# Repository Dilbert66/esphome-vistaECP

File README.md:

# Honeywell/Ademco Vista ECP ESPHome custom component and library

## Table of contents

- [Honeywell/Ademco Vista ECP ESPHome custom component and library](#honeywell-ademco-vista-ecp-esphome-custom-component-and-library)
  * [Table of contents](#table-of-contents)
  * [About the project](#about-the-project)
  * [Features](#features)
- [How to install](#how-to-install)
  * [⚠️ Warning!!! ⚠️](#⚠️-warning-⚠️)
  * [Prerequisites](#prerequisites)
    + [Identify Vista panel model](#identify-vista-panel-model)
  * [Project Structure and Wiring](#project-structure-and-wiring)
  * [Install ESPHome on the ESP device](#install-esphome-on-the-esp-device)
  * [Flash project into ESP device](#flash-project-into-esp-device)
    + [Language Adaptation](#language-adaptation)
      + [Option 1 (NEW)](#option-1--new-)
      + [Option 2 (OLD)](#option-2--old-)
  * [Connecting everything](#connecting-everything)
- [Miscellaneous](#miscellaneous)
  * [Example in Home Assistant](#example-in-home-assistant)
    + [Sample sensor configuration for card using mqtt](#sample-sensor-configuration-for-card-using-mqtt)
  * [HA Services](#ha-services)
  * [OTA updates](#ota-updates)
  * [MQTT integration](#mqtt-integration)
  * [Setting up the alarm panel keyboard card on HA](#setting-up-the-alarm-panel-keyboard-card-on-ha)
- [FAQ](#faq)
  * [Supported Models](#supported-models)
- [Report issue](#report-issue)
- [References](#references)
- [Author & Contributors](#author---contributors)

## About the project

This project allows you to monitor and control your old vista alarm panel over the internet through a cheap ESP device and an home automation platform such as Home Assistant or any other automation platform supporting the MQTT protocol.

If you like this project and wish to supplement my coffee intake, please click the button below to donate! Thank you!

Got a DSC PowerSeries panel? Have a look at the <a href="https://github.com/Dilbert66/esphome-dsckeybus">following project</a>.<br>

This is an implementation of an ESPHOME custom component and ESP Library to interface directly to Safewatch/Honeywell/Ademco Vista alarm systems using the ECP interface and very inexpensive ESP32 modules .  The ECP library code is based on the arduino source code from Mark Kimsal's repository located at  https://github.com/TANC-security/keypad-firmware.  It has been  completely rewritten as a class and adapted to work on the ESP platform using interrupt driven communications and pulse timing. A custom modified version of Peter Lerup's ESPsoftwareserial library (https://github.com/plerup/espsoftwareserial) was also used for the serial communications to work more efficiently within the tight timing of the ESP interrupt window. 

The panel sends various cmd packets such as the F7 (LCD display and status updates), FA (zone extenders, relay modules), FB (RF devices) and F2 (AUI touch screen diplays), F9 (Long range radio) and F6 (send keystrokes and cms).  These data cmds are used to capture all statuses from the panel as well as send keystrokes and cmds to the panel.

As far as writing on the bus and the request to send pulsing sequence, most documentation only discusses keypad traffic and this only uses the the 3rd pulse.  In actuality the pulses are used as noted below depending on the device type requesting to send:
```
Panel pulse 1. Addresses 1-7, expander board (07), etc
Panel pulse 2. Addresses 8-15 - zone expanders, relay modules
Panel pulse 3. Addresses 16-23 - keypads
```
For example, a zone expander that has the address 07, will send it's address on the first pulse only and will send nothing for the 2nd and 3rd pulse.  A keypad with address 16, will send a 1 bit pulse for pulse1 and pulse2 and then it's encoded address on pulse 3. This info was determined from analysis using a zone expander board and Pulseview to monitor the bus. 

If you are not familiar with ESPHome , I suggest you read up on this application at https://esphome.io and home assistant at https://www.home-assistant.io/.   The library class itself can be used outside of the esphome and home assistant systems.  Just use the code as is without the vistalalarm.yaml and vistaalarm.h files and call it's functions within your own application.  

This library is designed around the "external components" feature of ESPHome (https://esphome.io/components/external_components.html).  The previous version of this library was using the older "custom components" feature which is being deprecated.  Using external components is a much better alternative and allows for much easier install and customization.

To install, first copy the VistaAlarm.yaml file from here to your esphome directory. You can then edit it either directly or using the ESPHome dashboard to match your alarm panel setup.  The yaml is self explanatory.  Secondly, for the main library support code you have two choices:

 1: You can leave the yaml external_components source line uncommented and it will automatically fetch the required code from my esphome-components repository.  
 
 or alternatively:
 
 2: If you prefer a more manual approach, you can comment out the github source line and uncomment the source "my_components" line.  You will then need to create a matching my_components directory in your esphome home path.  Name it anything you like as long as it matches the source line in the yaml.  You then copy all content from the "components" directory located in repository https://github.com/Dilbert66/esphome-components/tree/main/ to this new directory.  Please note that for any future updates, you will again need to manually copy the files from the components repository to your esphome folder.

For multi partition support, it is important that you first program new keypad addresses assigned to each partiton you want to support using programs `*190` - `*196` on the vista panel.  Once done, assign these addresses to keypadaddr1 (partition1) , keypadaddr2 (partition2), keypaddr3 (partition3).  For unused partitions, leave the associated keypadaddrx config line at 0. 

##### Notes: 

* If you use the zone expanders and/or LRR functions, you might need to clear CHECK messages for the LRR and expanded zones from the panel on boot or restart by entering your access code followed by 1 twice. eg 12341 12341 where 1234 is your access code.

**Read more in the next wiki paragraphs for a detailed step by step guide.**

## Features

* Full zone expander emulation (4219/4229) which will give you  an additional 8 zones to the system per emulated expander plus associated relay outputs. Currently the library will provide emulation for 2 boards for a total of 16 additionals zones. You can even use free pins on the chip as triggers for those zones as well. 

* Full independent partition support. The firmware allows control and view status of all 3 partitions.

* Relay module emulation. (4204). The system can support 4 module addresses for a total of 16 relay channels. 

* Long Range Radio (LRR) emulation (or monitoring) statuses for more detailed status messages

* Zone status - Open, Alarmed, Closed and Bypass with named zones

* Arm, disarm or send any sequence of commands to the panel for any partition

* Status indicators - fire, alarm, trouble, armed stay, armed away, instant armed, armed night,  ready, AC status, bypass status, chime status,battery status, check status, zone and relay channel status field of individual partitions.

* Optional ability to monitor other devices on the bus such as keypads, other expanders, relay boards, RF devices, etc. This requires the #define MONITORTX to be uncommented in vista.h as well as the addition of two resistors (R4 and R5) to the circuit as shown in the schematic.   This adds another serial interrupt routine that captures and decodes all data on the green tx line.  If enabled this data will be used to update zone statuses for external modules.

The following services are published to home assistant for use in various scripts. 
```
alarm_disarm: Disarms the alarm with the user code provided, or the code specified in the configuration.
alarm_arm_home: Arms the alarm in home mode.
alarm_arm_away: Arms the alarm in away mode.
alarm_arm_night: Arms the alarm in night mode (no entry delay).
alarm_trigger_panic: Trigger a panic alarm.
alarm_trigger_fire: Trigger a fire alarm.
alarm_keypress: Sends a string of characters to the default partition. (Controlled by the keypad1 address)
alarm_keypress_partition: Sends a string of characters to any specified partition. (1, 2 or 3)
```

# How to install

## ⚠️ Warning!!! ⚠️

⚠️ **When opening the panel and dealing with the alarm panel itself throughout the reading of this wiki be careful as AC current is used to power the panel, make sure to switch it off before touching the terminals or any other part of the circuits.** ⚠️

##  Prerequisites

In order to install the project you need to:
- [Identify your Vista alarm panel model](#identify-vista-panel-model)
- Make sure to have a running instance of Home Assistant or any other home automation platform supporting MQTT protocol (or something else, but able to listen and publish on MQTT topics) // TO BE CHECKED
- [Get the needed components for the project and wire them](#project-structure-and-wiring)
- [Install ESPHome on the ESP device](#install-esphome-on-the-esp-device)
- Flash the project on the ESP device
- [Connect everything](#connecting-everything)

### Identify Vista panel model
Open the panel and check the interior side of the panel's door, there should be the wiring diagram indicating the Vista model right below (usually on bottom right or center). <br>

*Example: Vista-20P, Vista-20SE, Vista-20SEa, Vista-25IT, ...*<br>

If the wiring diagram is not present, check the circuit board. You should be able to see what model it is by looking either at the stamps/labels on the circuit board or by looking at the model on the CPU. The model here sometimes is in form of "SAVS**20P**5" or similar.<br> It is recommended to check also the circuit board even if you found the model on the wiring diagram, just to be sure that they match.

See image below, red arrows indicates where it could be.

Check [Supported Models](#supported-models) to get an overview of compatible models and continue to next section. 

If your device is not present in the list you could still try using one of the code versions available in the repository, **but the functioning is not guaranteed**.

Got a DSC PowerSeries panel? Have a look at the <a href="https://github.com/Dilbert66/esphome-dsckeybus">following project</a>.

##  Project Structure and Wiring

After you identified the vista panel's model then you can start preparing for the hardware part and the first HW part you need to get is an ESP device. In this case, it's highly
recommended that an ESP32 be used due to it's dual processor and increased available ram.<br>

Let's analyze the project structure.<br>

Currently the project is structured as follows:
- `master` branch: stable code - **recommended**
- `dev` branch: more updated code with new features, but WIP - **stability and functioning are not guaranteed**

For both branches you have the possibility to install them using Home Assistant or MQTT.<br>

If you have an Home Assistant instance running and you want to be able to fully control and monitor the panel through HA you will have to use the ESPHome yaml files for Home Assistant inside `src` folder. <br>

If instead you don't want to use Home Assistant, you can still use the component source code above, but you will have to use the sketch files inside the `MQTT-Example` folder and setup your home control software to process the MQTT topics.<br> // TO BE CHECKED

Select the branch and configuration/source code files you need.<br>

If you're unsure on what ESP model you need to get, then you can document at <a href="https://esphome.io/">ESPHome website</a>. *In theory*, any ESP device should work with ESPHome. Just make sure you have the GPIO numbers pin mapping, sometimes the pins don't match the ones reported in the pcb's silkscreen.<br>
*Example for the Wemos D1 R2 -> <a href="https://cyaninfinite.com/getting-started-with-the-wemos-d1-esp8266-wifi-board/">link</a>*

Now that you identified the panel, selected a source code and got an ESP device, it's time to choose a wiring configuration to the panel.

I've provided various working versions to fit within builders available parts or requirements.  None of these circuits need a pcb and can easily be built using point to point soldering on a proto board.

1. Non-isolated simple version.  Small parts count but resistor values are important.  Signal levels are dependent on components used. Output pulse will not be optimal due to optocoupler use.

2. Alternative version using transistors for both signal input and output.  Benefits are that signal quality will be optimal for both input and output. Resistor values are not critical. 
  Please note though that you have to configure your esphome yaml config accordingly to account for the signal inversion of this design. The other designs use the default settings.
YAML config:
```
  invert_mon: "false"
  invert_rx: "false"
  invert_tx: "true"
  input_mode_rx: INPUT_PULLUP
  input_mode_mon: INPUT_PULLUP
```

3. Ground isolated version

Notes: This version is the least recommended as it will load the ECP bus to a certain extent. It also does not provide the best signal output. This is all dependant on the bus it is connected to and the quality of the optocouplers used. Your mileage may vary.<br><br>
* Optocouplers should have a minimum CTR of 50. Recommendations are the 4N35 or TLP521. You can vary the resistor values for the simple version but keep the ratio similar for the voltage dividers R2/R3 and R4/R5. R1 should not be set below 150 ohm or 100ohm when using an ESP32. Resistor values are chosen to minimize load on ECP bus while still providing full output signals on the optocouplers. <br>
* My goal was to keep the design as simple as possible without causing any bus load or interference with maximum signal fidelity.  Since the transmit circuit required high side switching I opted to use an optocoupler since I had a few on hand and it simplified the amount of components needed but proved to have it's own issues as far as CTR requirements.  <br>

Read the notes on the drawings for more details.

Get the other components: 
- breadboard or PCB (if you prefer soldering)
- jumper cables
- 4-inputs screw terminal for the cables from the panel to the ESP (opt)
- resistors (you can use multiple resistors in series or parallel if you can't find kits with the exact value of the diagrams, i.e. 4.7KOhm can be obtained by using two resistors in parallel -> 100kohm + 5.1kohm =~ 4.8KOhm)
- optocouplers / transistors
- power supply or USB for the ESP device (highly recommended) or a 12V to 5V/3.3V regulator (to take the power from the panel)
- juction box (optional, to protect the ESP device if installed outside the panel)

Thanks to <a href="https://community.home-assistant.io/u/howardchen3">`@howardchen3`</a> there is a PCB layout of the ground-isolated version available at <a href="https://oshwlab.com/boobeechen/vistaesphome_copy">oshwlab</a> that could be used to send to a manufacturer. Read more on the site.

Wire the breadboard/PCB part according the wiring diagram you selected, but for the moment keep the ESP unplugged from both panel and breadboard/pcb since we're going to connect the ESP to the PC and it's not handy to have all the wires around. 

You should be in a situation like this now:

Esp is ready to be connected to the PCB/breadboard and the latter is ready to be connected at the panel.<br>
⚠️ **DO NOT CONNECT THEM YET** ⚠️

**Very important step**: Double check that the connections are ok (add some black tape to keep the loose connections in place if you opted for a breadboard). It is difficult to debug for HW problems once phisically attached to the panel or near to it as often the panels are not in comfy locations.

##  Install ESPHome on the ESP device
// TO BE CHECKED

This paragraph covers only the installation of the software that interacts with Home Assistant and ESPHome.

Connect the ESP device to the PC. Make sure you have the right drivers (CP2102 (square chip) or CH341 -> <a href="https://esphome.io/guides/physical_device_connection.html">ESPHome - physical device connection</a>) installed on your PC or ESPHome will not be able to recognize it.

Now you have two options:
1. Install a basic version of ESPHome on the ESP device (thorugh command line esphome or web.esphome.io) and then adopt it on ESPHome of your HA instance (in order to install right after the needed software over the air) **OR**
2. Install the final project on the device by using the ESPHome addon on HA (might be required to connect the ESP on the PC that is running HA)

Before proceeding with any of the two options, make sure to identify the right board and framework (opt) for your ESP device. Check the ESPHome website for more info.<br>

## Connecting everything 

⚠️ **Before continuing read [Warning notice](#⚠️-warning-⚠️)** ⚠️

Let's connect the ESP device to the breadboard or PCB and finally let's connect the breadboard/PCB to the panel. Depending on the configuration you selected, you need to connect the breadboard/PCB to the same keypad terminals of your existing physical keyboard **OR**, if you prefer, on the keypad terminals of another partition of your panel (in case of multi-partition panel).

**Make sure to keep the ESP device further from any RF receiver as the components and the ESP itself could cause interference.**

Power up the ESP device and check on Home Assistant. In a minute or so it should be ready and accessible from HA > ESPHome.

Ping the device address if having problems and double check the `project_config.yaml` file.

**Optional steps**

Cover the ESP device with a junction box or similar just to make a cover. Remember to keep at least two holes for some air venting.

Final result:

Note: Even the circuitry can be placed outside if you want. The wires from circuitry to the ESP are just for demo purposes, not related at all to the wiring diagrams. The power wire depends on the setup you chose, but it's recommended to have an external power supply.

# Miscellaneous
## Example in Home Assistant
#Note: The config below assumes an ESPHOME device named: "vistaalarm". Change the lines below to suit your own device name.

The returned statuses for Home Assistant are: armed_away, armed_home, armed_night, pending, disarmed,triggered and unavailable.  

Sample Home Assistant Template Alarm Control Panel configuration with simple services (defaults to partition 1):

```yaml
alarm_control_panel:
  - platform: template
    panels:
      safe_alarm_panel:
        name: "Alarm Panel"
        value_template: "{{states('sensor.vistaalarm_system_status')}}"
        code_arm_required: false
        
        arm_away:
           action: esphome.vistaalarm_alarm_arm_away
                  
        arm_home:
           action: esphome.vistaalarm_alarm_arm_home
          
        arm_night:
           action: esphome.vistaalarm_alarm_arm_night
            data_template:
              code: '{{code}}' #if you didnt set it in the yaml, then send the code here
          
        disarm:
           action: esphome.vistaalarm_alarm_disarm
            data_template:
              code: '{{code}}'                    
```

##  HA Services
Note:  The services for the HA API  will show up as esphome.<yourdevicename>.<servicenamefromlistbelow>
- Basic alarm services. These services default to partition 1:

	- "alarm_disarm", Parameter: "code" (access code)
	- "alarm_arm_home" 
	- "alarm_arm_night", Parameter: "code" (access code)
	- "alarm_arm_away"
	- "alarm_trigger_panic"
	- "alarm_trigger_fire"

- Intermediate command service. Use this service if you need more versatility such as setting alarm states on any partition:

	- "set_alarm_state",  Parameters: "partition","state","code"  where partition is the partition number from 1 to 8, state is one of "D" (disarm), "A" (arm_away), "S" (arm_home), "N" (arm_night), "P" (panic) or "F" (fire) and "code" is your panel access code (can be empty for arming, panic and fire cmds )

- Generic command service. Use this service for more complex control:

	- "alarm_keypress",  Parameter: "keys" where keys can be any sequence of keys accepted by your panel. For example to arm in night mode you set keys to be "xxxx33" where xxxx is your access code. 
    
	- "alarm_keypress_partition",  Parameters: "keys","partition" where keys can be any sequence of keys accepted by your panel and partition is  1 - 3. For example to arm in night mode  on partition 1 you set keys to be "xxxx33" and partition to be "1"  where xxxx is your access code.     
    
  - "set_zone_fault",Parameters: "zone","fault" where zone is a zone from 9 - 48 and fault is 0 or 1 (0=ok, 1=open)
      The zone number will depend on what your expander address is set to.

## OTA updates

In order to make OTA updates, it is recommended that the connection switch in the frontend be switched to OFF since the  ECP library is using interrupts and could cause issues with the update process.

## MQTT Support
If you would like to use MQTT communications with Homeassistant or alternatively use ESPHOME with other platforms that can support MQTT, you can modify the configuration to use the MQTT protocol instead of the native HA API integration.  This simply involves the addtion of an mqtt: configuration section in the yaml and to remove the api: section.   Please see the ESPHOME MQTT documentation more details: https://esphome.io/components/mqtt.html .  For an example on how to configure the alarm-panel-card to use MQTT services, please see the lovelace.yaml file.  

Command topic is "&lt;yoursystemnameinesphome&gt;/alarm/set"
	
Command payload for sending key commands: {"keys":"&lt;sequenceofkeys&gt;","partition":&lt;partition#&gt;}
	
Command payload to set an expander fault status: {"zone":&lt;zone#&gt;,"fault":&lt;on:off or 0:1&gt;}
	
Command payload to set an alarm state: {"state":"&lt;alarmstate&gt;","partition":&lt;partition#&gt;,"code":"&lt;accesscode&gt;"} - see set_alarm_state api command above for more details

Sensor data will follow the HA MQTT discovery format. See here for details: https://www.home-assistant.io/docs/mqtt/discovery/

If you prefer to use Arduino instead of ESPHome, I've also provided an Arduino example sketch in the mqtt_example folder.  Follow the instructions at the top of the file.

### Sample sensor configuration for card using mqtt.
Note, in this example the ESPHOME device name is "vistaalarm". Please change the lines below to match your own device name and field id's.

```yaml
# Partition 1 topics

mqtt:
  sensor:
    - name: "displayline1"
      state_topic: "vistaalarm/sensor/line1__ln1_1/state

    - name: "displayline2"
      state_topic: "vistaalarm/sensor/line2_ln2_1/state"

    - name: "vistaaway"
      state_topic: "vistaalarm/binary_sensor/away_partition_1/state"

    - name: "vistastay"
      state_topic: "vistaalarm/binary_sensor/stay_partition_1/state"

    - name: "vistaready"
      state_topic: "vistaalarm/binary_sensor/ready_partition_1/state"

    - name: "vistatrouble"
      state_topic: "vistaalarm/binary_sensor/trouble_partition_1/state"

    - name: "vistabypass"
      state_topic: "vistaalarm/binary_sensor/bypass_partition_1/state"

    - name: "vistachime"
      state_topic: "vistaalarm/binary_sensor/chime_partition_1/state"
      
    - name: "vistabeeps"
      state_topic: "vistaalarm/sensor/beeps_partition_1/state"    

    - name: "vistaac"
      state_topic: "vistaalarm/binary_sensor/ac_status/state" 

    - name: "vistabattery"
      state_topic: "vistaalarm/binary_sensor/battery_status/state"
      
    - name: "Front Door"
      state_topic: "vistaalarm/binary_sensor/front_door_z1/state"       

```

##  Setting up the alarm panel keyboard card on HA

I've added a sample lovelace alarm-panel card copied from the repository at https://github.com/GalaxyGateway/HA-Cards. I've customized it to work with this ESP library's services.   I've also added two new text fields that will be used by the card to display the panel prompts the same way a real keypad does. To configure the card, just place the `alarm-keypad-card.js` and `*.mp3` files from the ha_keypad_card folder into the `/config/www` directory of your homeassistant installation and add a new resource in your lovelace configuration pointing to `/local/alarm-keypad-card.js`. <br>
Add a reference to alarm-keypad-card.js in Lovelace. There’s two way to do that:<br>
1. Using UI:  go to settings (cog icon bottom left in sidebar menu), click on 'dashboards', click on top right 3 dots option then on Resources,
  bottom right 'add resource' option, in window, paste the url as '/local/alarm-keypad-card.js?id=1', select javascript module.

3. Using YAML: Add following code to lovelace section

```yaml
resources:
- url: /local/alarm-keypad-card.js?id=1
  type: module
```
*** NOTE *** :  Every time you update this file, you will need to increase the id=xx number in the url by 1 in order to force the browser to reload it.

You can then configure the card as shown below. Just substitute your service name to your application and choose one of the two chunks.

The first example is for using the esphome component in a multi partition environment.  The second uses MQTT.  The MQTT example can also support multiple partitions. 
Simply add "partition":xx in the json payload to select the desired partion where xx is the partition number.  If you don't enter a partition value, the default partition of 1 will be used.

```yaml
# EX1 - Partition 1 example - HA
type: custom:alarm-keypad-card
title: Vista_ESPHOME-partition1
disp_line1: sensor.vistaalarmtest_line1
disp_line2: sensor.vistaalarmtest_line2
service_type: esphome
service: vistaalarm_alarm_keypress_partition
status_A: AWAY
status_B: STAY
status_C: READY
status_D: BYPASS
status_E: TROUBLE
status_F: CHIME
status_G: ""
status_H: ""
sensor_A: binary_sensor.vistaalarmtest_away
sensor_B: binary_sensor.vistaalarmtest_stay
sensor_C: binary_sensor.vistaalarmtest_ready
sensor_D: binary_sensor.vistaalarmtest_bypass
sensor_E: binary_sensor.vistaalarmtest_trouble
sensor_F: binary_sensor.vistaalarmtest_chime
button_A: STAY
button_B: AWAY
button_C: BP LIST
button_D: BYPASS
button_F: null
button_G: ""
button_E: ""
button_H: DISARM
status_C_off_icon: mdi:circle-off-outline
status_C_on_icon: mdi:check-circle
status_C_color: green
status_E_color: orange
status_E_on_icon: mdi:alert
status_E_off_icon: mdi:triangle-outline
status_B_color: red
status_B_on_icon: mdi:shield-lock
status_B_off_icon: mdi:shield-off-outline
status_A_color: red
status_A_on_icon: mdi:shield-lock
status_A_off_icon: mdi:shield-off-outline

#all style settings are optional. These are the default colors
style:
  "--lcdbgcolordark": var(--input-fill-color)
  "--lcdtextcolordark": var(--primary-text-color)
  "--buttonbgcolordark": var(--input-fill-color)
  "--buttontextcolordark": var(--primary-color)
  "--buttonhovercolordark": var(--outline-hover-color)
  "--buttonactivecolordark": var(--secondary-text-color)
  "--sensorlabelcolordark": var(--accent-color));
  "--buttonfocuscolordark": var(--outline-color)
  "--sensoroffcolordark": var(--disabled-text-color)
  "--bordercolordark": var(--disabled-color)

  "--sensoroffcolorlight": var(--disabled-text-color)
  "--lcdbgcolorlight": var(--input-fill-color)
  "--lcdtextcolorlight": var(--primary-text-color)
  "--sensorlabelcolorlight": var(--accent-color));
  "--buttonbgcolorlight": var(--input-fill-color)
  "--buttontextcolorlight": var(--primary-color)
  "--buttonhovercolorlight": var(--outline-hover-color)
  "--buttonactivecolorlight": var(--secondary-text-color)
  "--buttonfocuscolorlight": var(--outline-color)
  "--bordercolorlight": var(--disabled-color)

cmd_A:
  keys: "12343"
  partition: 1
cmd_B:
  keys: "12342"
  partition: 1
cmd_C:
  keys: 1234600
  partition: 1
cmd_D:
  keys: 12346#
  partition: 1
cmd_E:
  keys: A
  partition: 1
cmd_H:
  keys: 12341
  partition: 1
cmd_F:
  keys: <
  partition: 1
cmd_G:
  keys: ">"
  partition: 1
key_0:
  keys: "0"
  partition: 1
key_1:
  keys: "1"
  partition: 1
key_2:
  keys: "2"
  partition: 1
key_3:
  keys: "3"
  partition: 1
key_4:
  keys: "4"
  partition: 1
key_5:
  keys: "5"
  partition: 1
key_6:
  keys: "6"
  partition: 1
key_7:
  keys: "7"
  partition: 1
key_8:
  keys: "8"
  partition: 1
key_9:
  keys: "9"
  partition: 1
key_star:
  keys: "*"
  partition: 1
key_pound:
  keys: "#"
  partition: 1
text_1: "OFF"
text_2: AWAY
text_3: STAY
text_4: MAX
text_5: TEST
text_6: BYPASS
text_7: INSTANT
text_8: CODE
text_9: CHIME
text_star: READY
text_pound: ""
text_0: ""
scale: 1
button_disabled_A: false
button_disabled_B: false
button_disabled_C: false
button_disabled_D: false
button_disabled_E: true
button_disabled_F: true
button_disabled_G: true
button_disabled_H: true
beep: sensor.vistaalarmtest_beeps
view_pad: true
view_display: true
view_status: true
view_status_2: true
view_bottom: false
button_left: false
vibration_duration: 5

```

```yaml
# EX2 - Partition 1 example - MQTT

type: 'custom:alarm-keypad-card'
title: Vista_MQTT
unique_id: vista1
disp_line1: sensor.displayline1
disp_line2: sensor.displayline2
scale: 1
service_type: mqtt
service: publish
status_A: AWAY
status_B: STAY
status_C: READY
status_E: BYPASS
status_D: TROUBLE
status_F: ''
status_G: ''
status_H: ''
sensor_A: sensor.vistaaway
sensor_B: sensor.vistastay
sensor_C: sensor.vistaready
sensor_E: sensor.vistabypass
sensor_D: sensor.vistatrouble
button_A: STAY
button_B: AWAY
button_C: DISARM
button_D: BYPASS
cmd_A:
  topic: Vista/Set
  payload: '{"keys":"12343","partition":"1"}
cmd_B:
  topic: Vista/Set
  payload: '{"keys":"12342","partition":"1"}
cmd_C:
  topic: Vista/Set
  payload: '{"keys":"12341","partition":"1"}
cmd_D:
  topic: Vista/Set
  payload: '{"keys":"12346#","partition":"1"}
key_0:
  topic: Vista/Set
  payload: '{"keys":"0","partition":"1"}
key_1:
  topic: Vista/Set
  payload: '{"keys":"1","partition":"1"}
key_2:
  topic: Vista/Set
  payload: '{"keys":"2","partition":"1"}
key_3:
  topic: Vista/Set
  payload: '{"keys":"3","partition":"1"}
key_4:
  topic: Vista/Set
  payload: '{"keys":"4","partition":"1"}
key_5:
  topic: Vista/Set
  payload: '{"keys":"5","partition":"1"}
key_6:
  topic: Vista/Set
  payload: '{"keys":"6","partition":"1"}
key_7:
  topic: Vista/Set
  payload: '{"keys":"7","partition":"1"}
key_8:
  topic: Vista/Set
  payload: '{"keys":"8","partition":"1"}
key_9:
  topic: Vista/Set
  payload: '{"keys":""9,"partition":"1"}
key_star:
  topic: Vista/Set
  payload: '{"keys":"*","partition":"1"}
key_pound:
  topic: Vista/Set
  payload: '{"keys":"#","partition":"1"}
text_1: 'OFF'
text_2: AWAY
text_3: STAY
text_4: MAX
text_5: TEST
text_6: BYPASS
text_7: INSTANT
text_8: CODE
text_9: CHIME
text_star: READY
text_pound: ''
text_0: ''  
view_pad: true
view_display: true
view_status: true
view_status_2: true
view_bottom: false
button_left: false
beep: sensor.vistabeeps
vibration_duration: 5
```

# FAQ

1. How do I use the Trace Analyzer for deeper investigation?

Connect the pulseview channel D0 to the yellow line input on the D1 ESP input pin and the pulseview channel D1 to the green line monitor input D5 pin on ESP and then finally ground to the common ground on the ESP side. You don't need to monitor VCC or the ESP D2 output since that will also be seen on the green line monitor input at D5. Make sure you don't connect the channel inputs to any voltage higher than around 5 volts.

You should not be sharing ground between the panel and the esp if you used the optocoupler isolated schematic to build your circuit. if you did, it won't hurt anything, it's just not needed.

The setup file is really just the decoder setup so you that you can actually see the data being sent. It's attached below.
Just unzip it and load it into PulseView software by selecting "Restore session setup" from the menu. Ensure you connect your device first before running PulseView so that it picks it up on start up. (it will show up as a Saelea 8 channel). Once it starts your session, you will see 8 inputs. Once you restore the saved session setup, you will see 3 channels and 2 decoders. One for the panel (yellow line) and one for the keypad (green line). You'll need to run the capture twice to actually capture data. Seems like the first time after loading a session, it does not see the channels but the second run is fine.

<a href="https://github.com/Dilbert66/esphome-vistaECP/files/7150101/vistaecp2.zip">vistaecp2.zip</a>

Once you have about 1 minute or so of data you can then click the save button to save the session. It will create an *.sr file.
zip that and attach it to the issue.

### sample sensor configuration for card using mqtt

2. What is LRR?

LRR = Long Range Radio. IP or GSM interface and monitored by a central monitoring station.

3. What is an address?

A zone number. Zone number = Address. //TO BE CHECKED

4. How do I setup the expanders?

// TO BE CHECKED

5. What is the access code?

Your 4 digit secret number to arm/disarm the system. e.g. 1234

6. What is quickArm?

It will the hashtag instead of your access code for the arm command. E.g. it will send #3 instead of 12343 to enable "stay" mode.

7. What is RFMsg?

It is a string variable that will be populated with the messages from your RF devices, if any. Read more in the yaml configuration section (rfSerialLookup).<br>
In general, the RF message will contain the serial number and a status byte (with the sensor data).<br>
```
  bit 1 - ?
  bit 2 - Battery (0=Normal, 1=LowBat)
  bit 3 - Heartbeat (Sent every 60-90min) (1 if sending heartbeat)
  bit 4 - ?
  bit 5 - Loop 3 (0=Closed, 1=Open)
  bit 6 - Loop 2 (0=Closed, 1=Open)
  bit 7 - Loop 4 (0=Closed, 1=Open)
  bit 8 - Loop 1 (0=Closed, 1=Open)
```
// TO BE CHECKED

8. How do I open an issue?

See [How to](#report-issue) section.

```

## Supported Models

As of today:

|  **Model** |  **Source Code**  |
|:----------:|:-----------------:|
| Vista 20P  | vistaEcpInterface |
| Vista 20SE | vista20SE         |
| Vista 25IT | vista20SE         |
| Vista120 | vistaEcpInterface - // TO BE CHECKED |
| Vista128bpt/250bpt | vistaEcpInterface - // TO BE CHECKED |
| | |
| | |
| | |
| | |

# Report issue

First: search for your issue into the closed and open issues in the repo, if you don't find anything, open a new issue specifying:<br>
- Panel Model
- Used ESP model
- Used wiring diagram
- YAML config (the necessary parts)
- Issue
- Installed sensors (if relevant)
- What you've tried
- Logs

# References

## References 

You can checkout the links below for further reading and other implementation examples. Some portions of the code in the repositories below was used in creating the library.
* https://github.com/TANC-security/keypad-firmware
* https://github.com/cweemin/espAdemcoECP
* https://github.com/TomVickers/Arduino2keypad/

This project is licensed under the `Lesser General Public License` version `2.1`, or (at your option) any later version as per it's use of other libraries and code. Please see `COPYING.LESSER` for more information.

# Author & Contributors

- @Dilbert66 (Author)
- @appleguru (Contributor)
- @nitej (Contributor)
- @rcmurphy (Contributor)
- @jdev-homeauto (Contributor)
- @lorenzodeveloper (Contributor)

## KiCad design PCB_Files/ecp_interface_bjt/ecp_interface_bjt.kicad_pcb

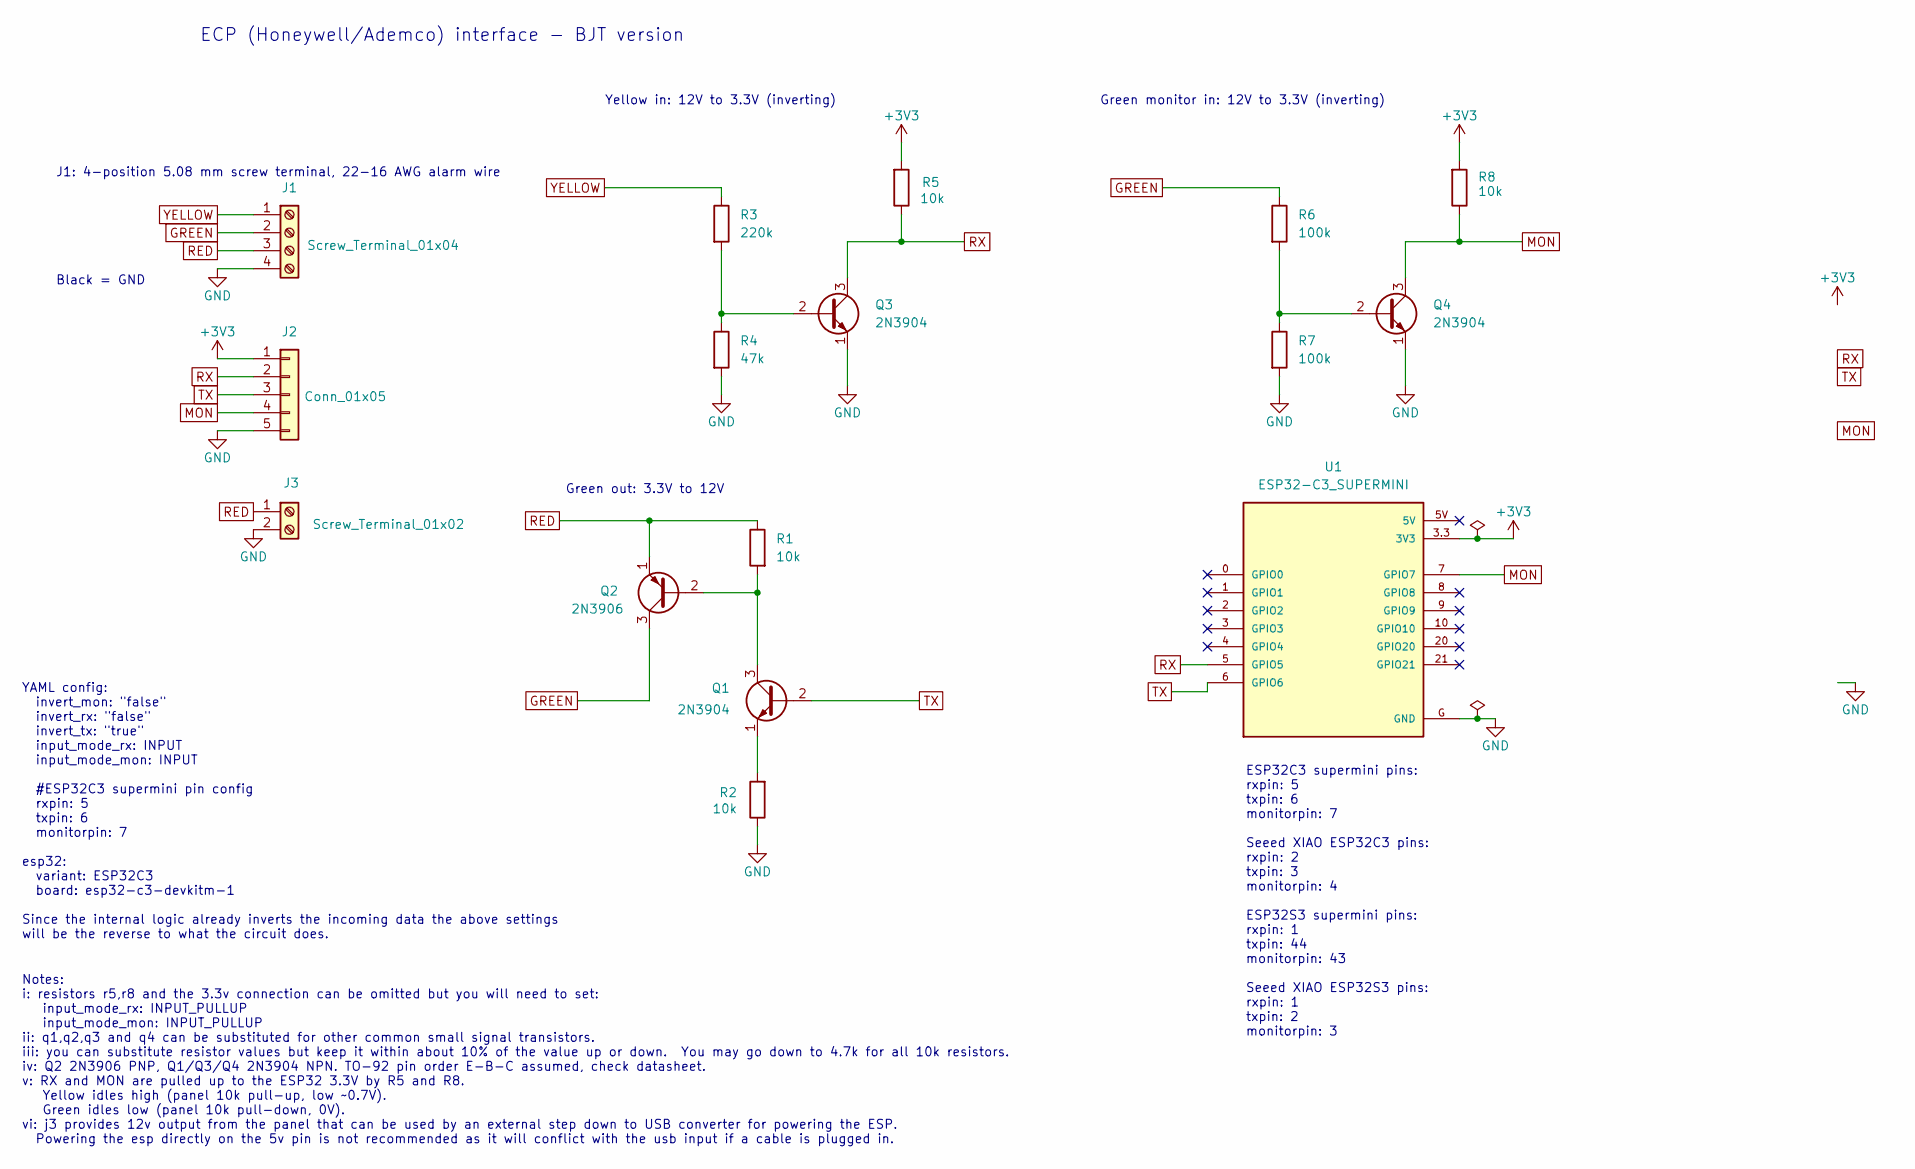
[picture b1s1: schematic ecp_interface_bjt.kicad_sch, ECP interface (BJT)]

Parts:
J1: Screw_Terminal_01x04; TerminalBlock_MetzConnect_Type101_RT01604HBWC_1x04_P5.08mm_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
J2: Conn_01x05; PinHeader_1x05_P2.54mm_Vertical
J3: Screw_Terminal_01x02; TerminalBlock_MetzConnect_Type059_RT06302HBWC_1x02_P3.50mm_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
Q1, Q3, Q4: 2N3904; TO-92_HandSolder
Q2: 2N3906; TO-92_HandSolder
R1, R2, R5, R8: 10k; R_Axial_DIN0207_L6.3mm_D2.5mm_P10.16mm_Horizontal
R3: 220k; R_Axial_DIN0207_L6.3mm_D2.5mm_P10.16mm_Horizontal
R4: 47k; R_Axial_DIN0207_L6.3mm_D2.5mm_P10.16mm_Horizontal
R6, R7: 100k; R_Axial_DIN0207_L6.3mm_D2.5mm_P10.16mm_Horizontal
U1: ESP32-C3_SUPERMINI; MODULE_ESP32-C3_SUPERMINI_PIN1

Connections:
+3V3: J2.1, R5.2, R8.2, U1.3.3 (3V3)
GND: J1.4, J2.5, J3.2, Q3.1 (E), Q4.1 (E), R2.1, R4.2, R7.2, U1.G (GND)
GREEN: J1.2, Q2.3 (C), R6.1
MON: J2.4, Q4.3 (C), R8.1, U1.7 (GPIO7)
unnamed: Q1.3 (C), Q2.2 (B), R1.2
unnamed: Q1.1 (E), R2.2
unnamed: Q3.2 (B), R3.2, R4.1
unnamed: Q4.2 (B), R6.2, R7.1
RED: J1.3, J3.1, Q2.1 (E), R1.1
RX: J2.2, Q3.3 (C), R5.1, U1.5 (GPIO5)
TX: J2.3, Q1.2 (B), U1.6 (GPIO6)
YELLOW: J1.1, R3.1

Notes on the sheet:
J1: 4-position 5.08 mm screw terminal, 22-16 AWG alarm wire
Yellow in: 12V to 3.3V (inverting)
Notes: i: resistors r5,r8 and the 3.3v connection can be omitted but you will need to set: input_mode_rx: INPUT_PULLUP input_mode_mon: INPUT_PULLUP ii: q1,q2,q3 and q4 can be substituted for other common small signal transistors. iii: you can substitute resistor values but keep it within about 10% 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
ECP (Honeywell/Ademco) interface - BJT version
Black = GND
Green monitor in: 12V to 3.3V (inverting)
ESP32C3 supermini pins: rxpin: 5 txpin: 6 monitorpin: 7 Seeed XIAO ESP32C3 pins: rxpin: 2 txpin: 3 monitorpin: 4 ESP32S3 supermini pins: rxpin: 1 txpin: 44 monitorpin: 43 Seeed XIAO ESP32S3 pins: rxpin: 1 txpin: 2 monitorpin: 3
Green out: 3.3V to 12V
YAML config: invert_mon: "false" invert_rx: "false" invert_tx: "true" input_mode_rx: INPUT input_mode_mon: INPUT #ESP32C3 supermini pin config rxpin: 5 txpin: 6 monitorpin: 7 esp32: variant: ESP32C3 board: esp32-c3-devkitm-1 Since the internal logic already inverts the incoming data the above setti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

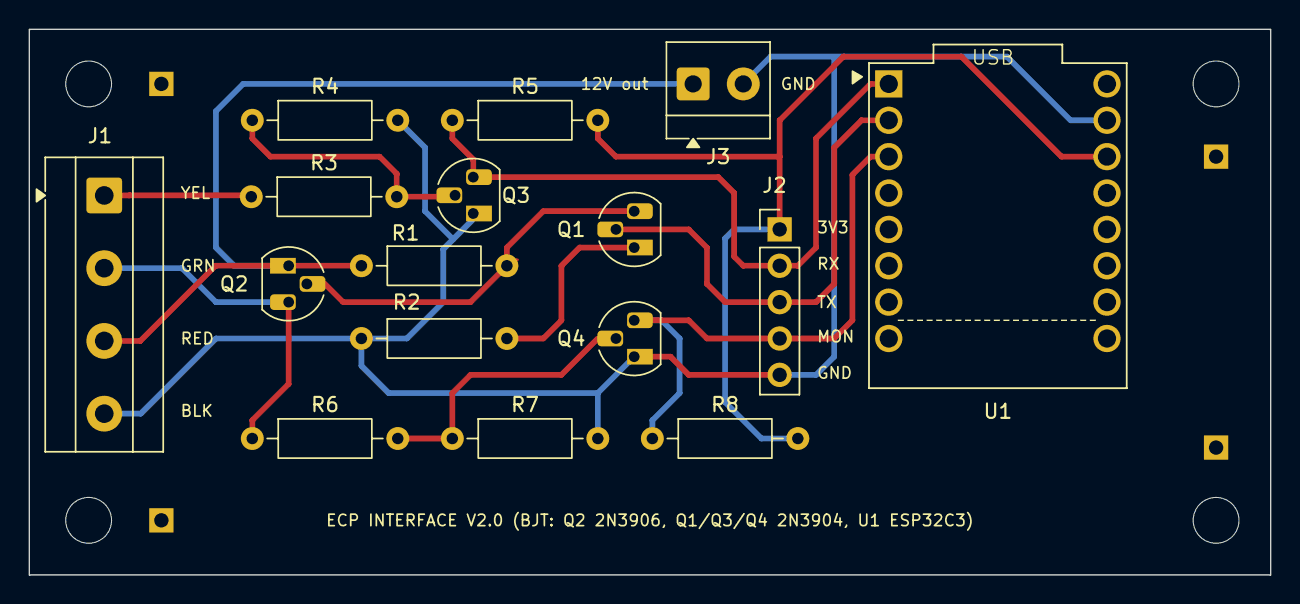
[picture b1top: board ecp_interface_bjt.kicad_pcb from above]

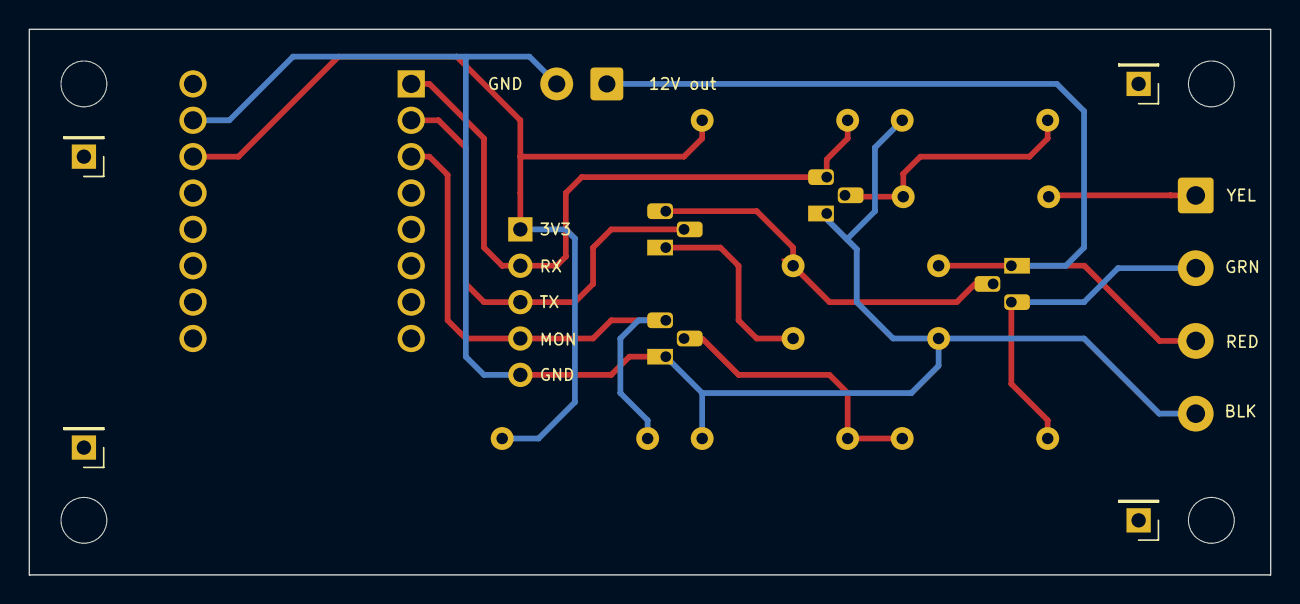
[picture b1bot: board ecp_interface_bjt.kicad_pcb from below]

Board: 2 copper layers, 86.7 x 38.1 mm, 24 parts (4 on the bottom side), 12 nets.

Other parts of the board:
H1, H2, H3, H4: MountingHole_3.2mm_M3
js: support pin; PinHeader_1x01_P2.54mm_Vertical
js#2, js#3, js#4: support pin; PinHeader_1x01_P2.54mm_Vertical

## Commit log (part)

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2022-04-11 - fixed issue with system flag statuses
2022-04-11 - fixed incorrect battery flag logic
2022-04-13 - simplified binary zone sensor example by adding new dedicated callback - updated example yaml
2022-04-16 - modified partition check to allow zone messages to pass through
2022-04-16 -added missed vistalarm.h changes
2022-04-18 - removed last change to display all zones. Limit to partition assigned to virtual keypad only
2022-04-18 - added ability to enter lookup strings as character arrays instead of strings to simplify adding non-english type messages
2022-04-18 - modified lookup strings to be editable as ascii characters
2022-04-18 - small change to lookup
2022-04-18 - small change
2022-04-18 - only display ascii line for zone messages
2022-04-18 - removed unecessary armed prompt check
2022-04-19 - removed high range filter from prompt characters to allow international characters
2022-04-19 - removed filter in SE lib
2022-04-19 - modified translate code to filter out non ascii as they cause issues. Add ability to translate specific characters
2022-04-19 - translation change to fully remove problematic asci characters
2022-04-20 - reverted to string lookup entries due to the non-ascii characters changing the string
2022-05-02 - corrected missing check status - added missing armed sensor statement - corrected away status update
2022-05-02 - changed alarm setting services to now be required to send the partition to support multi partions. - added field refresh to rf and beeps to force them to a known value at start and to clear the pre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
2022-05-02 - small tweak on trouble status logic - added problem device type to trouble
2022-05-09 Added HA card simulating a 6139 keypad
2022-05-11 - added real time clock to data logging
2022-05-12 - added example commented api encryption config
2022-06-15 - added ability to trigger panic keys (zone 95,96,99) by sending keys F,M or P (fire,medical,police)
2022-06-15 - remove uneeded code
2022-10-03 - typo in alarmstatus assignment
2022-10-03 - removed uneeded service. - removed duplicate entry in yaml file
2022-10-03 - changed f7 to fe command processing
2022-10-03 - default se to partition 1 - added missing keypadaddress section to single partition example yaml
2022-10-18 - enabled zones from different partitions to be processed
2022-11-07 - changed zone type from uint8_t to int in order to support zones above 255 for large vista systems
2022-11-14 - added new cmd debug check.
2022-11-15 - removed uneeded var
2022-11-15 - small sanity check with zone allocation in preg logic
2022-12-08 - added function to retrieve zone from f7 message for bypass,fault, fire for systems with more than 99 zones
2022-12-08 - add auto disconnect from ecp on ota transfer
2022-12-09 - remove zone fetch in check message since this refers more to devices
2022-12-12 - changed getpartitionsfromamask to support keypad address with addresses other than 16-23
2022-12-12 - revert last 2400 baud change in fb command for vista20se
2022-12-17 - fix rf chksum logic to correct index
2022-12-17 - correct index.
2022-12-17 - removed errant f7 ack pulse
2022-12-17 - fix issue with RF packet checksum
2022-12-18 - added new cmd F0 processing
2022-12-18 - unknown cmd process tweak to switch baud
2022-12-18 - removed 2400 setting from unknown cmd
2022-12-18 - better unknown cmd support
2022-12-18 - small update to unknown cmd processing to limit lag
2022-12-18 - tweak to unknown cmd processing to deal with missed FA cmds at wrong baud rate
2022-12-19 - added modification to support vista250bpt style sync pulses
2022-12-19 - added missing directory
2022-12-19 - removed problematic unknown cmd byte processing
2022-12-19 - added hightime check to ensure we capture ack byte correctly
2022-12-20 - correct f0 ext response data
2022-12-20 - correct issue with RTS address mask in ISR
2022-12-20 - f0 cmd response fix
2022-12-20 - added maxZones and maxPartitions to yaml config. Allows to configure panel maximum zones and partitions from the main yaml config file without needing to edit defines in vistalarm.h
2022-12-21 - switched rf serialnumber lookup table to substitution instead of global variable for easier configuration. Change your yaml.
2022-12-21 - fix check for empty rfseriallookup
2022-12-21 - add default partition to configuration in yaml
2022-12-21 - correct missing default arg
2022-12-22 - fix incorrect buffer memory allocation
2022-12-22 - small tweak in cmd handling for the vista20se
2022-12-25 - small tweak to isr to set low bit on 4800
2022-12-25 - adjust pulse marker
2022-12-26 - rewrote prompt matching to ensure we capture the correct term
2022-12-27 - streamline serial routines to better capture parity and stop bits
2022-12-27 - update vista20se serial functions
2022-12-27 - fixed issue with some missed stop bit on last character
2022-12-27 - serial tweak
2022-12-28 - replaced regex search with for loops to reduce lag
2022-12-30 - increased status cmds byte handling to 5 for some vista20se systems
2022-12-31 - added check for twinned cmds
2023-01-01 - correct unknown cmd f8 lenght
2023-01-02 - switched to micros instead of millis for more accurate bit measurment
2023-01-03 - fix issue with wrong file copied. - fix micros seconds delay
2023-01-03 - remove debug code
2023-01-03 - added some debug code for message packets
2023-01-04 - comment out debug define to stop printing of the ff cmds
2023-01-04 - improved serial functions by adding parity checking and filtering of bogus data bytes - switched to micros of interval measurements in isr
2023-01-05 - separated localized panel language text to panelText.h - cleaned up beep div naming
2023-01-05 - moved panel translations to a separate language file for the vistase
2023-01-06 Minor fix on README.md
2023-01-06 Minor fix on README.md pt2
2023-01-06 Added table of contents
2023-01-07 Added new language adaptation options, RF msg lookup explanation and other stuff
2023-01-07 Added mqtt example and modified other parts of the README file
2023-01-07 Added one FAQ
2023-01-08 - add ability to use library with esphome mqtt or arduino sketch as well as the esphome api
2023-01-08 - fix incorrect kpaddr variable
2023-01-11 - updated readme with updated example
2023-01-11 - updated vista20se with working files
2023-01-11 - fixed incorrect vistaalarm.h file for vista20se
2023-01-12 - update vista20se to tested version
2023-01-12 - turn off debug for vista20se
2023-01-12 - added Arduino MQTT example sketch for the Vista20Se
2023-01-12 - cleaned up some code for the SE
2023-01-13 - more cleanups
2023-01-17 - fixed up some compile warnings - added standalone telegram and virtual keypad sketch example
2023-01-18 - added notify flag to virtualkeypad
2023-01-18 - added some helper tips to sketch
2023-01-18 - status messages updates in sketch
2023-01-19 - added support for other methods in telgram lib - increased message size
2023-01-19 - clean up formatting
2023-01-24 - code formatting changes - renamed includes to lowercase - other small fixes
2023-01-24 - fix file case
2023-01-24 - test commit after rename
2023-01-27 - some vistaalarmkeypad tweaks - remove unecessary variables in include
2023-01-27 - display changes for virtualkeypad - added force refresh
2023-01-28 - clear refresh flag
2023-01-28 - correct refresh for prompt
2023-01-28 - fix missed typo
2023-01-28 - refresh all lights and display on partition change
2023-01-29 - remove intermittent connection error on login in index.html
2023-02-20 - added W as additional status for armed away (A default)
2023-02-25 - test library.json file
2023-03-29 - Corrected missing trbl message in paneltext.h
2023-03-29 - update deprecated icache_ram_attr to iram_attr
2023-03-30 - removed some warnings
2023-03-31 - fixed incorrect type conversion
2023-03-31 ICACHE_RAM_ATTR change to IRAM_ATTR to fix compile warnings.
2023-04-06 - migrated custom keypad from polymer to lit - added config option button_left to control location of button column
2023-04-06 - fixed card titles. - removed uneeded toggles attribute
2023-08-03 - changed debug prints to info level
2023-10-20 - changed status unavailable to not ready
2023-10-23 - added simplified yaml config setup which should be less confusing to setup
2023-10-29 - added better support for unknown cmd handling - fixed issue with cmd handling when dealing with process delays
2023-10-29 - increased bit buffer size
2023-10-31 - restore lrr/rf message auto clear after 30seconds
2023-10-31 - added ability to monitor special zones such as device faults and extended zones
2023-10-31 - added fault and alarm status checks for extended zones
2023-11-02 - reduce serial buffer for memory optimizations
2023-11-02 - reduce buffer size - add zero clear in cmd handling
2023-11-02 - added a zero check in onexp for loop
2023-11-03 - modified rf serial entry to use RF serial device zone and loop# as programed in *56. No need to use masks. See the yaml for more details
2023-11-03 - added low battery monitoring if you have programmed rf devices
2023-11-03 - remove some warnings
2023-11-04 - added check for missing binary sensor callback that was causing crashes
2023-11-06 - initial external components implementation
2023-11-07 - added dsc component - bug fixes
2023-11-08 - removed dsc component
2023-11-08 - removed dependence of prompts for zone statuses
2023-11-08 - refresh timing change
2023-11-08 - config file fixes
2023-11-09 - added link to yaml
2023-11-09 - remove gpio section
2023-11-09 - added zone text sensor example
2023-11-09 - added text sensor example for zone
2023-11-09 - readme revisions for new version
2023-11-09 - remove merge artifacts
2023-11-09 - remove another merge artifact
2023-11-09 - remove another merge artificact
2023-11-13 - removed merge artifacts
2023-11-13 - redo the mqtt documentation section
2023-11-13 -redo mqtt documenation section
2023-11-13 - revisit mqtt documenation again
2024-01-10 - use shortcut for armed away, bypass, stay modes in lovelace.yaml
2024-05-05 - yaml config update
2024-05-14 Update README.md
    Updated HA sensor config for mqtt
2024-05-31 - added tag
2024-06-02 - update yaml to new settings
2024-06-03 - update readme and yaml config
2024-06-12 - revert to using binary_sensor and text_sensor for custom fields
2024-06-29 - upadted yaml with new template_alarm platform config
2024-10-24 - updated sample yaml and readme with new sensor id's for ap
2024-10-31 - corrected ota section
2024-10-31 - commented out on_begin due to bug in esphome
2024-12-06 - updated config to new code version
2024-12-07 - removed requirement on mg_lib component
2024-12-23 - added optimistic option
2024-12-30 Update VistaAlarm.yaml
    in github URL, master branch is now main
2025-01-11 - added haptic feedback on buttons
2025-01-12 - add haptic feedback to keypad
2025-01-12 - increased opacity on touch
2025-03-17 - added custom_component to vista20se
2025-03-20 - upgraded keypad card with configurable icons
2025-03-20 - upgraded keypad card with configurable status icons
2025-03-20 - update example
2025-03-21 - use color as status parameter on keypad
2025-03-24 - updated to lit 4.0 - added ability to cusomtomize card colors from config
2025-03-24 - added ability to customize card colors in config
2025-03-26 - more cosmetic tweaks
2025-03-26 - change font
2025-03-30 - added ability to modify card colors
2025-03-31 - added ability to customize styling and colors
2025-07-16 - added cusom_services option to api section
2025-08-28 - correct invalid platform on button example
2025-08-28 - fix incorrect template on button example
2025-08-28 - comment out section
2025-10-30 - added sensor check on lines - updated default sensor names
2025-10-30 - updated sensor names to match example yaml
2025-11-07 - changed friendly name to match name
2025-11-14 - display beeps
2025-12-06 [webkeypad] fixed issue with updates on ha 2025.11 [webkeypad] added stub config
2026-03-11 - update vista20se code to compile on latest esphome
2026-03-13 - updated vista20se yaml to new format

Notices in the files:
README.md:
This project is licensed under the `Lesser General Public License` version `2.1`, or (at your option) any later version as per it's use of other libraries and code. Please see `COPYING.LESSER` for more information.
